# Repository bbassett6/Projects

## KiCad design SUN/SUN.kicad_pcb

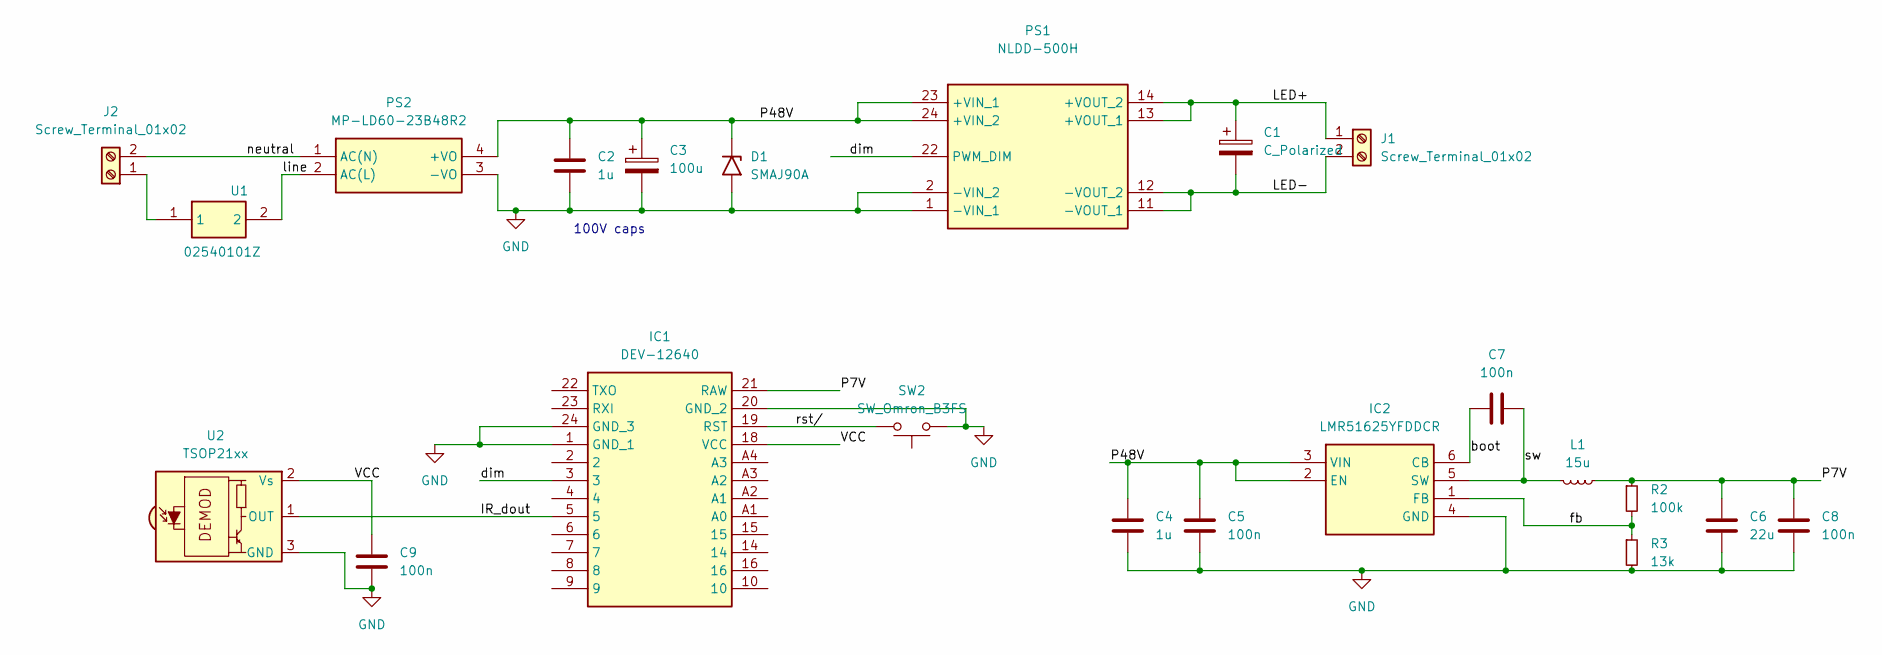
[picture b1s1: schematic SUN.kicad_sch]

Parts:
C1: C_Polarized; CP_Radial_D6.3mm_P2.50mm
C2, C4: 1u; C_1206_3216Metric
C3: 100u; CP_Radial_D10.0mm_P5.00mm
C5, C7, C8, C9: 100n; C_0603_1608Metric
C6: 22u; C_1210_3225Metric
D1: SMAJ90A; D_SMA
IC1: DEV-12640; DEV12640; Manufacturer_Part_Number DEV-12640; Mouser Part Number 474-DEV-12640
IC2: LMR51625YFDDCR; SOT95P280X110-6N; Manufacturer_Part_Number LMR51625YFDDCR; Mouser Part Number 595-LMR51625YFDDCR
J1, J2: Screw_Terminal_01x02; TerminalBlock_WAGO_804-102_1x02_P5.00mm_45Degree
L1: 15u; L_Coilcraft_XAL4030-XXX
PS1: NLDD-500H; NLDD500H; Manufacturer_Part_Number NLDD-500H; Mouser Part Number 709-NLDD-500H
PS2: MP-LD60-23B48R2; MPLD6023B48R2; Manufacturer_Part_Number MP-LD60-23B48R2
R2: 100k; R_0603_1608Metric
R3: 13k; R_0603_1608Metric
SW2: SW_Omron_B3FS; SW_SPST_Omron_B3FS-100xP
U1: 02540101Z; Manufacturer_Part_Number 02540101Z; Mouser Part Number 576-02540101Z
U2: TSOP21xx; Vishay_MOLD-3Pin

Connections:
/IR_dout: IC1.5, U2.1 (OUT)
/LED+: C1.1, J1.1, PS1.13 (+VOUT_1), PS1.14 (+VOUT_2)
/LED-: C1.2, J1.2, PS1.11 (-VOUT_1), PS1.12 (-VOUT_2)
/P7V: C6.1, C8.1, IC1.21 (RAW), L1.1, R2.1
/P48V: C2.1, C3.1, C4.1, C5.1, D1.1 (A1), IC2.2 (EN), IC2.3 (VIN), PS1.23 (+VIN_1), PS1.24 (+VIN_2), PS2.4 (+VO)
/VCC: C9.1, IC1.18 (VCC), U2.2 (Vs)
/boot: C7.1, IC2.6 (CB)
/dim: IC1.3, PS1.22 (PWM_DIM)
/fb: IC2.1 (FB), R2.2, R3.1
/line: PS2.2 (AC(L)), U1.2
/neutral: J2.2, PS2.1 (AC(N))
/rst/: IC1.19 (RST), SW2.2
/sw: C7.2, IC2.5 (SW), L1.2
GND: C2.2, C3.2, C4.2, C5.2, C6.2, C8.2, C9.2, D1.2 (A2), IC1.1 (GND_1), IC1.20 (GND_2), IC1.24 (GND_3), IC2.4 (GND), PS1.1 (-VIN_1), PS1.2 (-VIN_2), PS2.3 (-VO), R3.2, SW2.1, U2.3 (GND)
unnamed: J2.1, U1.1

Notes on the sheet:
100V caps

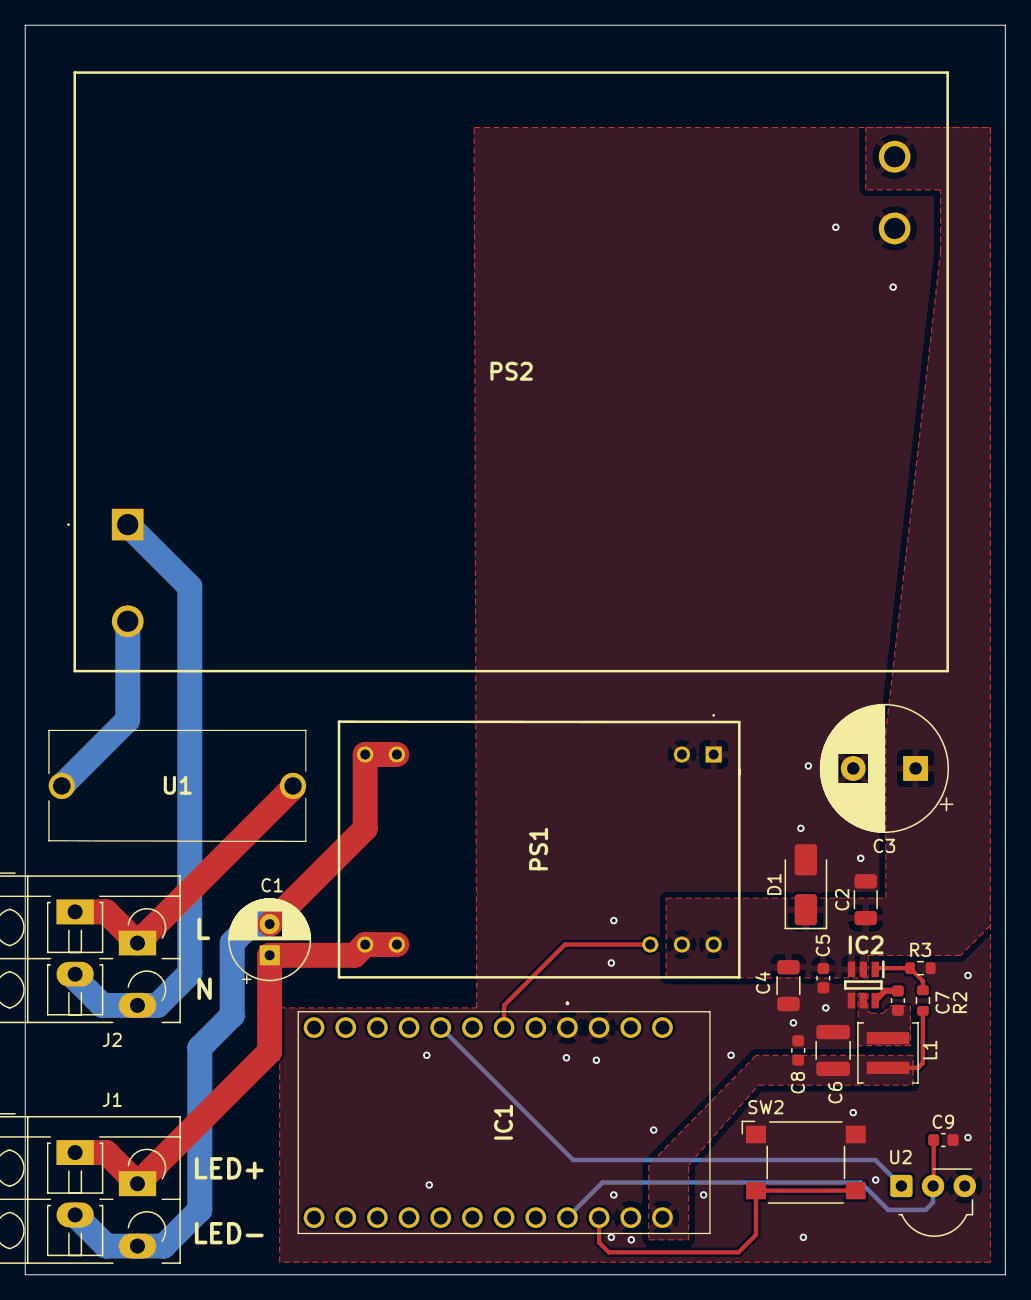
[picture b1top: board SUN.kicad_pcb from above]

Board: 2 copper layers, 78.6 x 100.2 mm, 22 parts (0 on the bottom side), 15 nets.

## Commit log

2025-09-04 not sure what these were
    hmm
2025-09-04 board completed
    board completed and ordered
2025-09-16 bom changes
2025-09-28 initial working 2 stage
    getting 6.7db with 4+3b stage. some maybe weirdness though
2025-09-28 9.96b with 3 stages
    now getting 9.96b with 3 stages. 2 stages are 4B3R and final 4b flash quantizer
2025-09-29 it works. 13b with no non idealities
    finally works and gives 80db snr
    it goes down pretty fast with capacitor mismatch. no transfer function yet
2025-09-29 now with transfer function
    74db snr with some non idealities
    saving before I run with more granularity
2025-09-29 done for tonight I hope
    works and has still 73.36db snr with non idealities
2025-09-30 final device works and specifications are reasonably set
